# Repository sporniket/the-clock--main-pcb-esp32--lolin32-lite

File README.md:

# Main board for The Clock supporting WEMOS Lolin32 lite

> [WARNING] Please read carefully this note before using this project. It contains important facts.

Content

1. What is **Main board for The Clock supporting WEMOS Lolin32 lite**, and when to use it ?
2. What should you know before using **Main board for The Clock supporting WEMOS Lolin32 lite** ?
3. How to use **Main board for The Clock supporting WEMOS Lolin32 lite** ?
4. Known issues
5. Miscellanous

## 1. What is **Main board for The Clock supporting WEMOS Lolin32 lite**, and when to use it ?

**Main board for The Clock supporting WEMOS Lolin32 lite**, as the name imply, is the hardware implementation of a seven-segment digital clock, synchronized to the network time using SNTP ; this particular implementation targets an ESP32 based development board known as _WEMOS Lolin32 lite_, that as been programmed using the esp32 based firmware.

### Licence

**Main board for The Clock supporting WEMOS Lolin32 lite** is published under the Creative Commons CC0 license. You can find a copy of the licence there : https://creativecommons.org/publicdomain/zero/1.0/legalcode

You can copy, modify, distribute and perform the work, even for commercial purposes, all without asking permission.

**Main board for The Clock supporting WEMOS Lolin32 lite** is distributed in the hope that it will be useful, but WITHOUT ANY WARRANTY; without even the implied warranty of MERCHANTABILITY or FITNESS FOR A PARTICULAR PURPOSE.

### Release notes

#### Version 0.1.1

* Fixed : missing pull-up resistors for SDA/SCL

#### Version 0.1.0

Initial release, includes an ambient light sensor using an LDR.

## 2. What should you know before using **Main board for The Clock supporting WEMOS Lolin32 lite** ?

**Main board for The Clock supporting WEMOS Lolin32 lite** is made using Kicad 7.

> Do not use **Main board for The Clock supporting WEMOS Lolin32 lite** if this project is not suitable for your project.

## 3. How to use **Main board for The Clock supporting WEMOS Lolin32 lite** ?

### From sources

To get the latest available work, one must clone the git repository, build and install the package.

	git clone --recurse-submodules https://github.com/sporniket/the-clock--main-pcb-esp32--lolin32-lite.git

Then, open the project with Kicad 7.

## 4. Known issues
See the [project issues](https://github.com/sporniket/the-clock--main-pcb-esp32--lolin32-lite/issues) page.

## 5. Miscellanous

### Report issues
Use the [project issues](https://github.com/sporniket/the-clock--main-pcb-esp32--lolin32-lite/issues) page.

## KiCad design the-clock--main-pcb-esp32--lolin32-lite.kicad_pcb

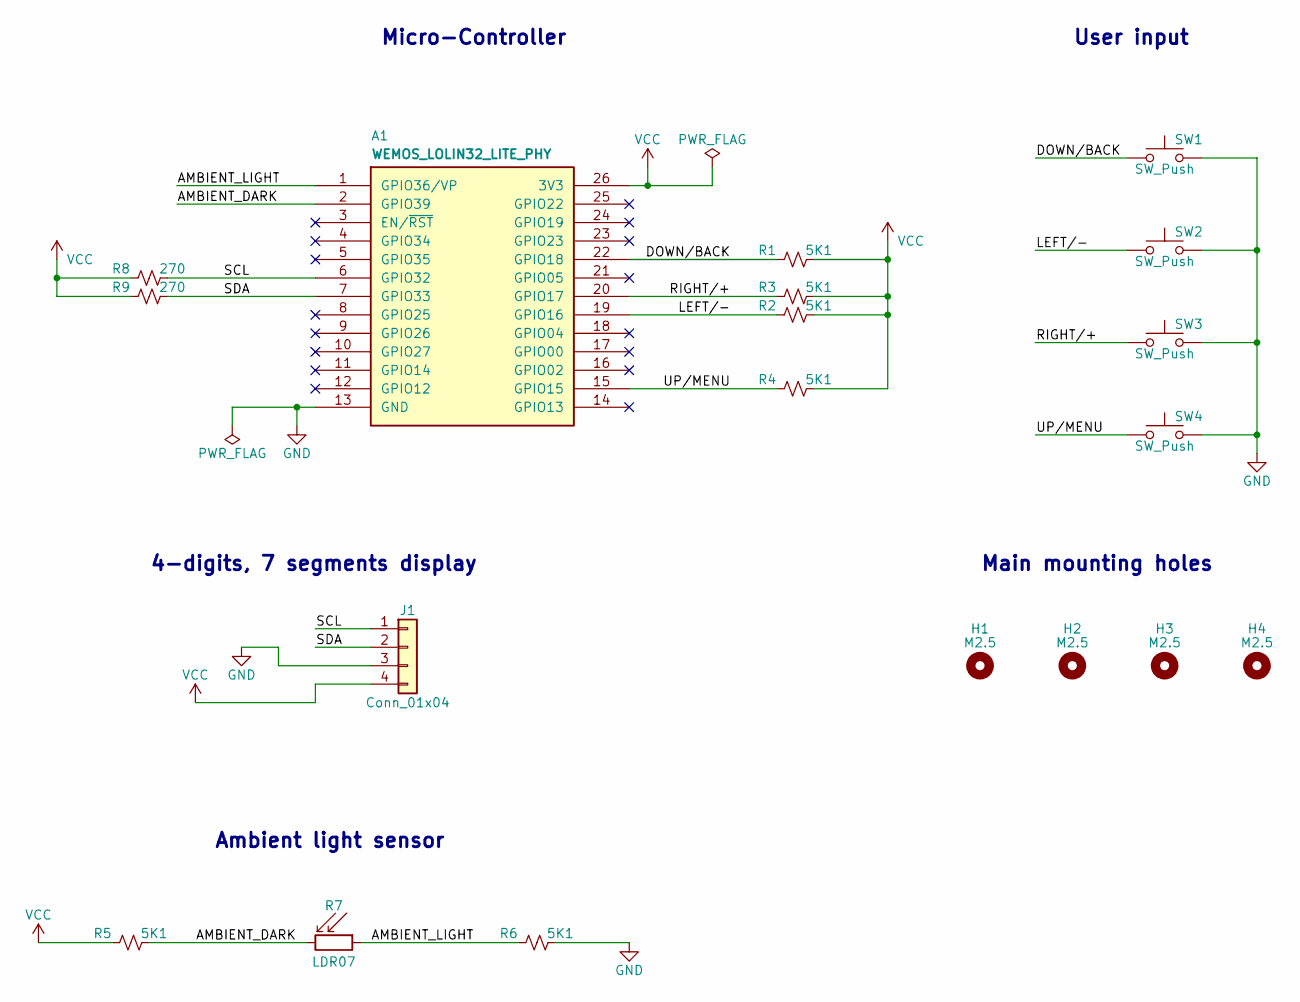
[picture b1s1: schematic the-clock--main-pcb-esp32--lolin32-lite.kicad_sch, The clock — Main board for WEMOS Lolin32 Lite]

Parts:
A1: WEMOS_LOLIN32_LITE_PHY; DIP-26_900_WEMOS_LOLIN32_LITE
H1, H2, H3, H4: M2.5; MountingHole_2.7mm_M2.5
J1: Conn_01x04; TM1637_7_segments_4_digits_clock_i2c
R1, R2, R3, R4, R5, R6: 5K1; Passive_THT_resistor_W2.54mm_L10.16mm
R7: LDR07; R_LDR_5.1x4.3mm_P3.4mm_Vertical
R8, R9: 270; Passive_THT_resistor_W2.54mm_L10.16mm
SW1, SW2, SW3, SW4: SW_Push; SW_PUSH_6mm_H13mm

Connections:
/AMBIENT_DARK: A1.2 (GPIO39), R5.2, R7.2
/AMBIENT_LIGHT: A1.1 (GPIO36/VP), R6.1, R7.1
/DOWN/BACK: A1.22 (GPIO18), R1.1, SW1.1
/LEFT/-: A1.19 (GPIO16), R2.1, SW2.1
/RIGHT/+: A1.20 (GPIO17), R3.1, SW3.1
/SCL: A1.6 (GPIO32), J1.1, R8.2
/SDA: A1.7 (GPIO33), J1.2, R9.2
/UP/MENU: A1.15 (GPIO15), R4.1, SW4.1
GND: A1.13 (GND), J1.3, R6.2, SW1.2, SW2.2, SW3.2, SW4.2
VCC: A1.26 (3V3), J1.4, R1.2, R2.2, R3.2, R4.2, R5.1, R8.1, R9.1

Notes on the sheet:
Micro-Controller
Main mounting holes
4-digits, 7 segments display
Ambient light sensor
User input

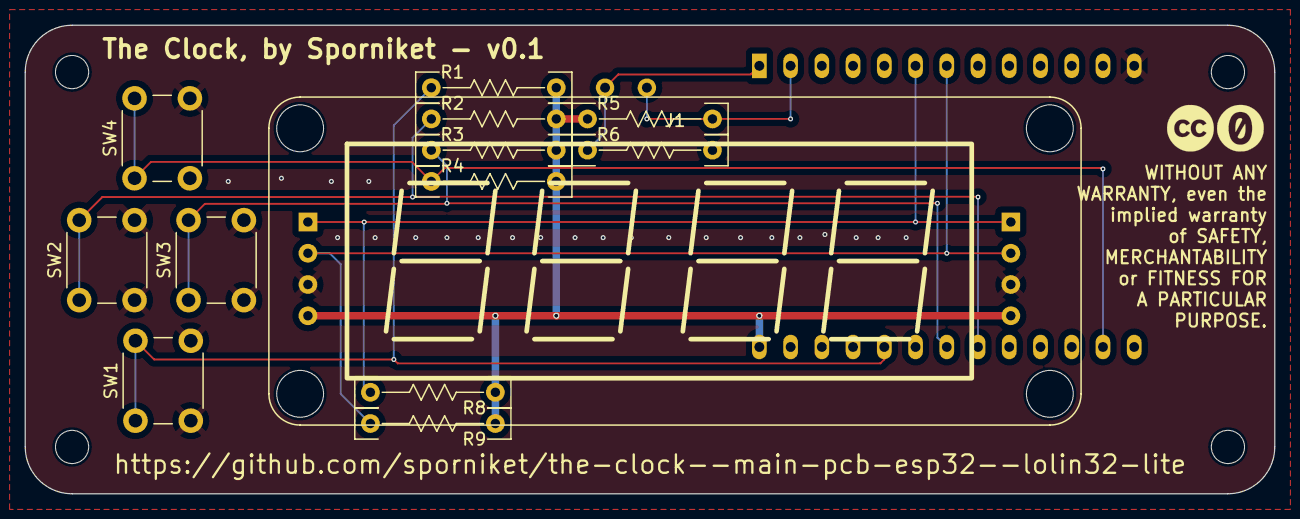
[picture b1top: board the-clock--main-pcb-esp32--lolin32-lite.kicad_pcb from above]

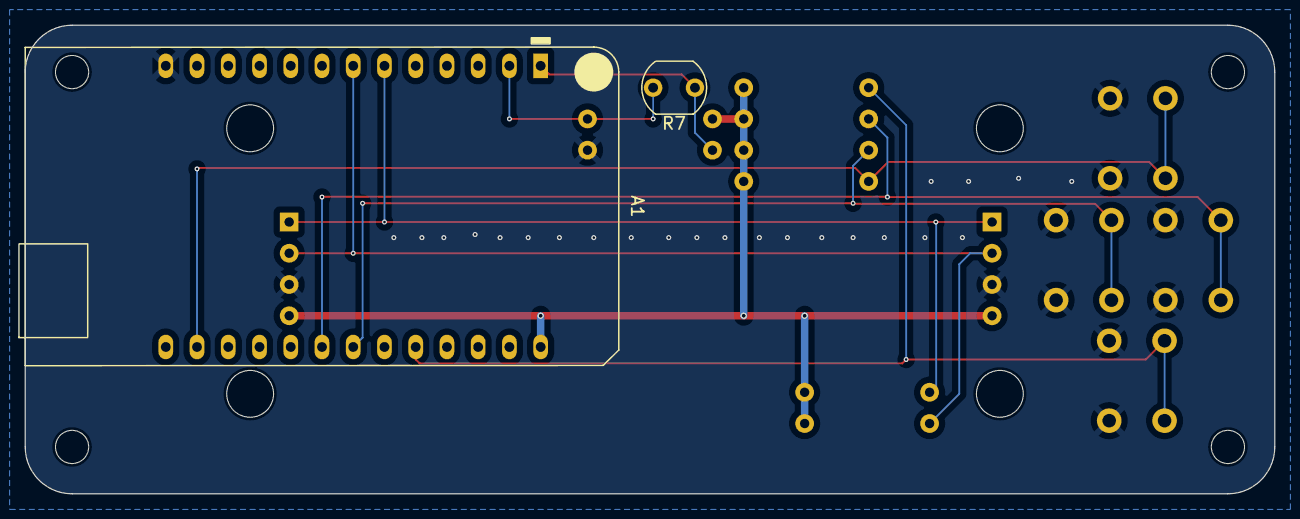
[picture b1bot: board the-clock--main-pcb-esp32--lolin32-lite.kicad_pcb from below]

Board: 2 copper layers, 101.6 x 38.1 mm, 19 parts (2 on the bottom side), 10 nets.

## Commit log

2023-11-19 first prototype, quick schematics, pcb guideline and cut
2023-11-20 added footprint : TM1637 based 7-segments digital clock 4 digits
2023-11-21 updated footprint library : Wemos Lolin32 lite
2023-11-21 remove useless hole (already included by the footprint)
2023-11-21 assigned footprints
2023-11-21 design rules
2023-11-21 fix user input and pull-ups
2023-11-21 pcb session 2023-11-21T22:50:08+01:00 : almost done
2023-11-22 provision ambient light sensor
2023-11-22 pcb -- added ambient light sensor
2023-11-22 finished silkscreen
2023-11-22 prepare release
2023-11-22 prepare release : README
2023-11-22 export settings
2023-12-02 Fixed : missing pull-up resistors for SDA/SCL
2023-12-05 Prepare next release
2023-12-06 update readme -- gallery
